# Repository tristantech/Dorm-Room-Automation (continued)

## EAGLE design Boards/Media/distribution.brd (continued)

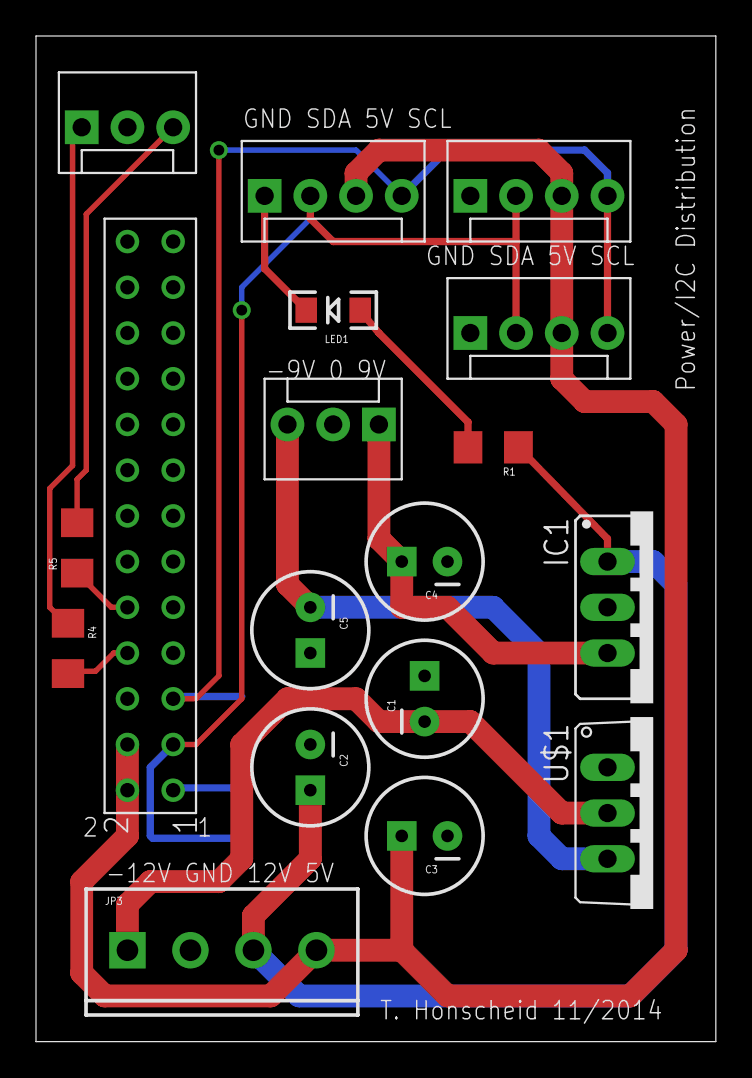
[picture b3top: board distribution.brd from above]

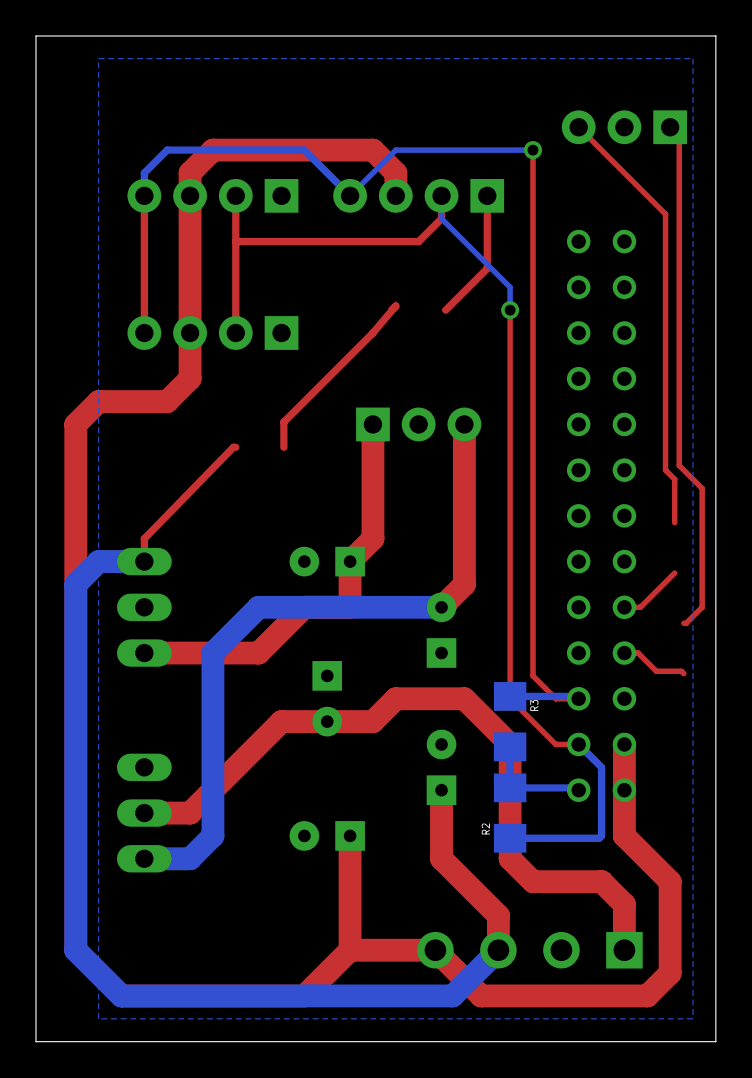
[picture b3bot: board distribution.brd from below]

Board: 2 copper layers, 37.8 x 55.9 mm, 20 parts (2 on the bottom side), 14 nets.

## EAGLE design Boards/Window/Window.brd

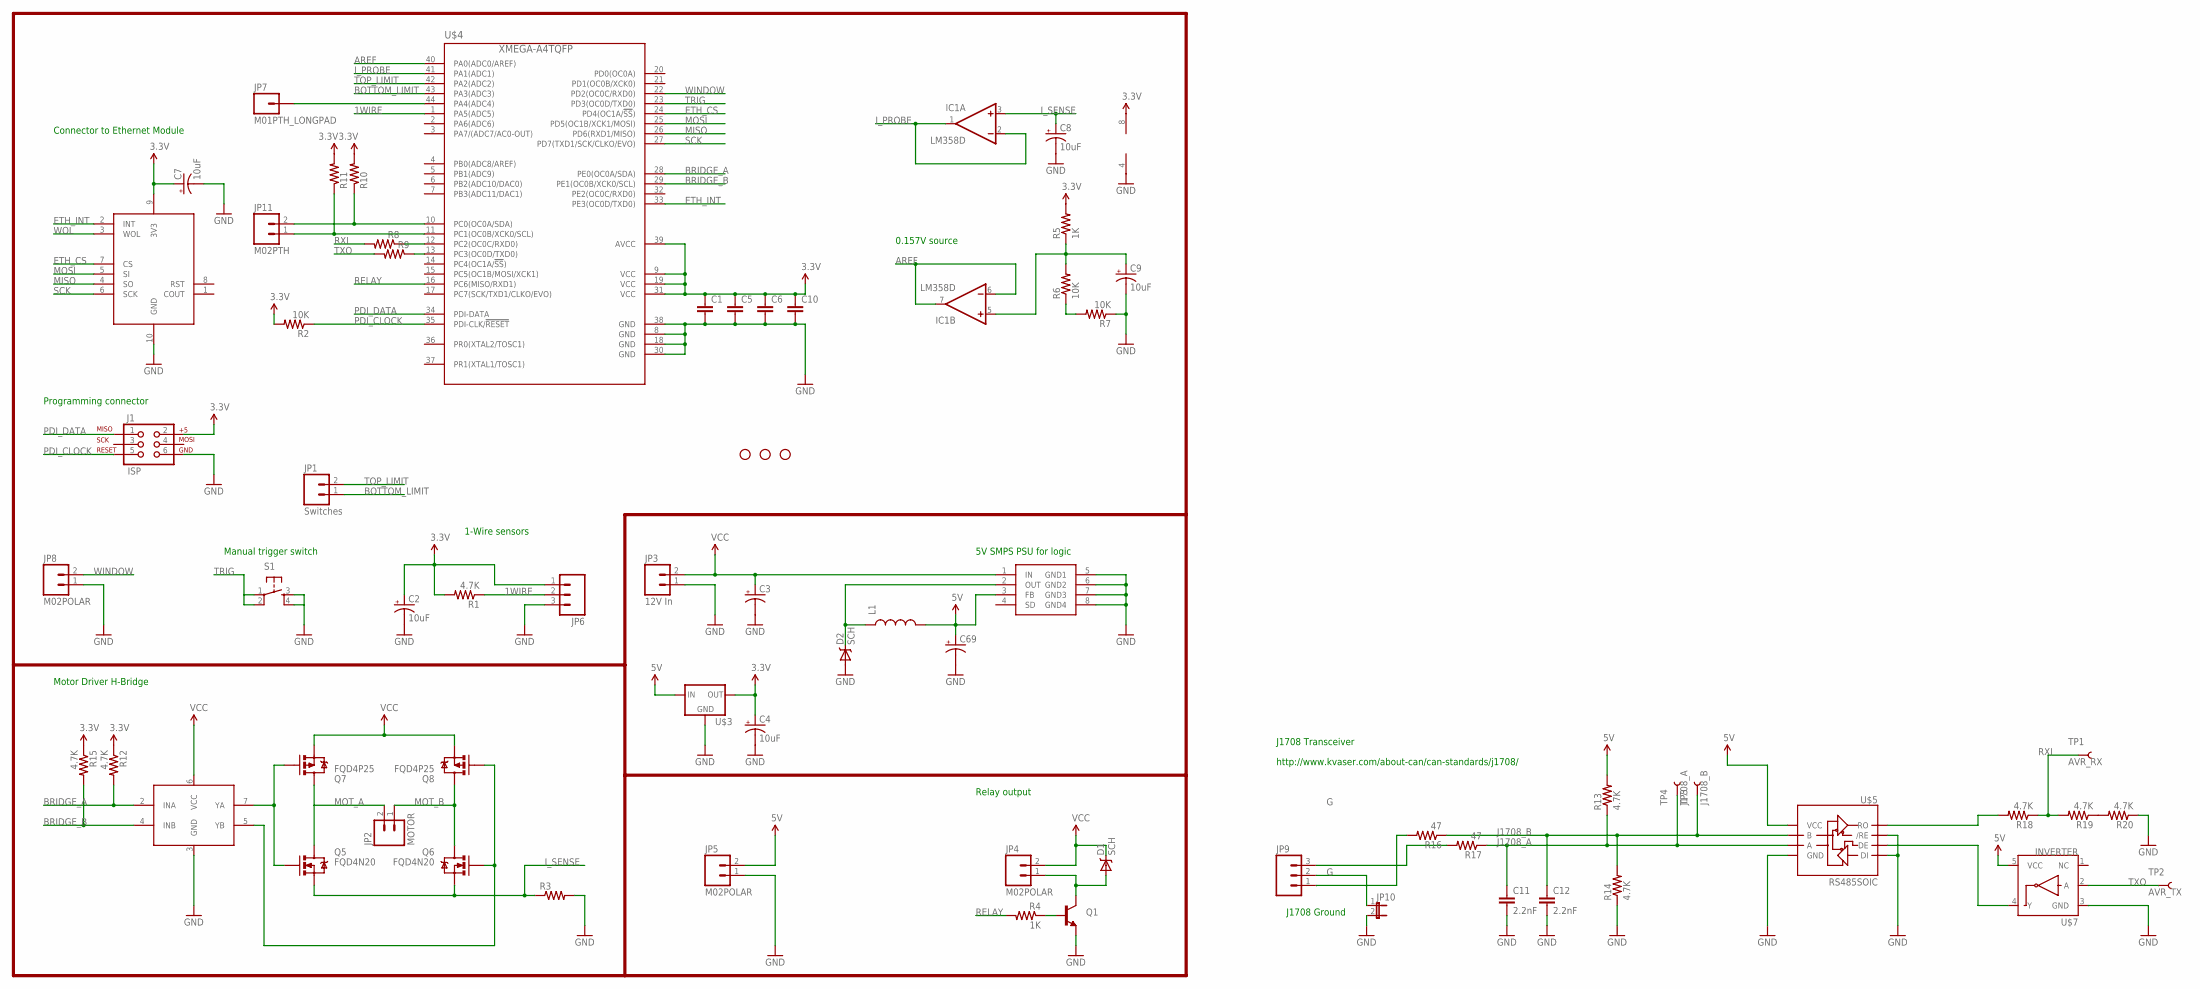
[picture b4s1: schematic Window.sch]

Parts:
C1, C5, C6, C10: CAP0603-CAP; 0603-CAP
C2, C4, C7, C8, C9: 10uF; EIA3216
C3, C69: CAP_POLPTH1; CPOL-RADIAL-100UF-25V
C11, C12: 2.2nF; 0603-CAP
D1, D2: SCH; SMA-DIODE
IC1: LM358D; SO08
J1: ISP; 2X3
JP1: Switches; SCREWTERMINAL-3.5MM-2
JP2: MOTOR; SCREWTERMINAL-3.5MM-2
JP3: 12V In; SCREWTERMINAL-3.5MM-2
JP4, JP5, JP8: M02POLAR; MOLEX-1X2
JP6, JP9: M03POLAR; MOLEX-1X3
JP7: M01PTH_LONGPAD; 1X01_LONGPAD
JP10: JUMPER-2PTH; 1X02
JP11: M02PTH; 1X02
L1: INDUCTOR1206H*; INDUCTOR-1206
Q1: TRANSISTOR_NPNSOT23; SOT23
Q5, Q6: FQD4N20; DPAK
Q7, Q8: FQD4P25; DPAK
R1, R12, R13, R14, R15, R18, R19, R20: 4.7K; 1206
R2, R6, R7: 10K; 1206
R3: RESISTORPTH-1W; AXIAL-0.6
R4, R5: 1K; 1206
R8, R9, R10, R11: RESISTOR0603-RES; 0603-RES
R16, R17: 47; 1206
S1: TAC_SWITCHPTH; TACTILE-PTH
STANDOFF2, STANDOFF3, STANDOFF4: STAND-OFF
TP1: AVR_RX; PAD.03X.05
TP2: AVR_TX; PAD.03X.05
TP3: J1708_B; PAD.03X.05
TP4: J1708_A; PAD.03X.05
U$1: ETHMODULE; 2X5
U$2: AP1509-33; SOIC-8
U$3: V_REG_MIC2920; SOT223
U$4: XMEGA-A4TQFP; TQFP44
U$5: RS485SOIC; SO08
U$6: 4427; SOIC-8
U$7: INVERTER; SOT23-5

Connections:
1WIRE: JP6.2, R1.1, U$4.1 (PA5(ADC5))
3.3V: C1.1, C2.A (+), C4.A (+), C5.1, C6.1, C7.A (+), C10.1, IC1.8 (V+), J1.2, JP6.1, R1.2, R2.2, R5.2, R10.2, R11.2, R12.1, R15.1, U$1.9 (3V3), U$3.3 (OUT), U$4.9 (VCC), U$4.19 (VCC), U$4.31 (VCC), U$4.39 (AVCC)
5V: C69.1 (+), JP5.2, L1.P$2 (2), R13.2, U$2.3 (FB), U$3.1 (IN), U$5.8 (VCC), U$7.5 (VCC)
AREF: IC1.6 (-IN), IC1.7 (OUT), U$4.40 (PA0(ADC0/AREF))
BOTTOM_LIMIT: JP1.1, U$4.43 (PA3(ADC3))
BRIDGE_A: R12.2, U$4.28 (PE0(OC0A/SDA)), U$6.2 (INA)
BRIDGE_B: R15.2, U$4.29 (PE1(OC0B/XCK0/SCL)), U$6.4 (INB)
COUT: U$1.1 (COUT)
ETH_CS: U$1.7 (CS), U$4.24 (PD4(OC1A/!SS!))
ETH_INT: U$1.2 (INT), U$4.33 (PE3(OC0D/TXD0))
G: JP9.2, JP10.1
GND: C1.2, C2.C (-), C3.2 (-), C4.C (-), C5.2, C6.2, C7.C (-), C8.C (-), C9.C (-), C10.2, C11.2, C12.2, C69.2 (-), D2.A, IC1.4 (V-), J1.6, JP3.1, JP5.1, JP6.3, JP8.1, JP10.2, Q1.2 (E), R3.P$2 (2), R7.1, R14.1, R20.1, S1.3, S1.4, U$1.10 (GND), U$2.5 (GND1), U$2.6 (GND2), U$2.7 (GND3), U$2.8 (GND4), U$3.2 (GND), U$4.8 (GND), U$4.18 (GND), U$4.30 (GND), U$4.38 (GND), U$5.2 (/RE), U$5.4 (DI), U$5.5 (GND), U$6.3 (GND), U$7.3 (GND)
I_PROBE: IC1.1 (OUT), IC1.2 (-IN), U$4.41 (PA1(ADC1))
I_SENSE: C8.A (+), IC1.3 (+IN), Q5.3 (S), Q6.3 (S), R3.P$1 (1)
J1708_A: C11.1, R13.1, R17.1, TP4.P$1, U$5.6 (A)
J1708_B: C12.1, R14.2, R16.1, TP3.P$1, U$5.7 (B)
MISO: U$1.4 (SO), U$4.26 (PD6(RXD1/MISO))
MOSI: U$1.5 (SI), U$4.25 (PD5(OC1B/XCK1/MOSI))
MOT_A: JP2.2, Q5.4 (D), Q7.4 (D)
MOT_B: JP2.1, Q6.4 (D), Q8.4 (D)
unnamed: JP11.2, R10.1, U$4.10 (PC0(OC0A/SDA))
unnamed: JP11.1, R11.1, U$4.11 (PC1(OC0B/XCK0/SCL))
unnamed: D2.C, L1.P$1 (1), U$2.2 (OUT)
unnamed: R8.1, U$4.12 (PC2(OC0C/RXD0))
unnamed: D1.A, JP4.1, Q1.3 (C)
unnamed: JP9.1, R16.2
unnamed: R6.1, R7.2
unnamed: Q5.1 (G), Q7.1 (G), U$6.7 (YA)
unnamed: Q1.1 (B), R4.1
unnamed: C9.A (+), IC1.5 (+IN), R5.1, R6.2
unnamed: R9.1, U$4.13 (PC3(OC0D/TXD0))
unnamed: JP9.3, R17.2
unnamed: R18.2, U$5.1 (RO)
unnamed: R19.1, R20.2
unnamed: Q6.1 (G), Q8.1 (G), U$6.5 (YB)
unnamed: U$5.3 (DE), U$7.4 (Y)
unnamed: JP7.1, U$4.44 (PA4(ADC4))
PDI_CLOCK: J1.5, R2.1, U$4.35 (PDI-CLK/!RESET)
PDI_DATA: J1.1, U$4.34 (PDI-DATA)
RELAY: R4.2, U$4.16 (PC6(MISO/RXD1))
RST: U$1.8 (RST)
RXI: R8.2, R18.1, R19.2, TP1.P$1
SCK: U$1.6 (SCK), U$4.27 (PD7(TXD1/SCK/CLKO/EVO))
TOP_LIMIT: JP1.2, U$4.42 (PA2(ADC2))
TRIG: S1.1, S1.2, U$4.23 (PD3(OC0D/TXD0))
TXO: R9.2, TP2.P$1, U$7.2 (A)
VCC: C3.1 (+), D1.C, JP3.2, JP4.2, Q7.3 (S), Q8.3 (S), U$2.1 (IN), U$6.6 (VCC)
WINDOW: JP8.2, U$4.22 (PD2(OC0C/RXD0))
WOL: U$1.3 (WOL)

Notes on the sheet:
Connector to Ethernet Module
Programming connector
1-Wire sensors
Motor Driver H-Bridge
Manual trigger switch
Relay output
0.157V source
5V SMPS PSU for logic
J1708 Ground
J1708 Transceiver
http://www.kvaser.com/about-can/can-standards/j1708/

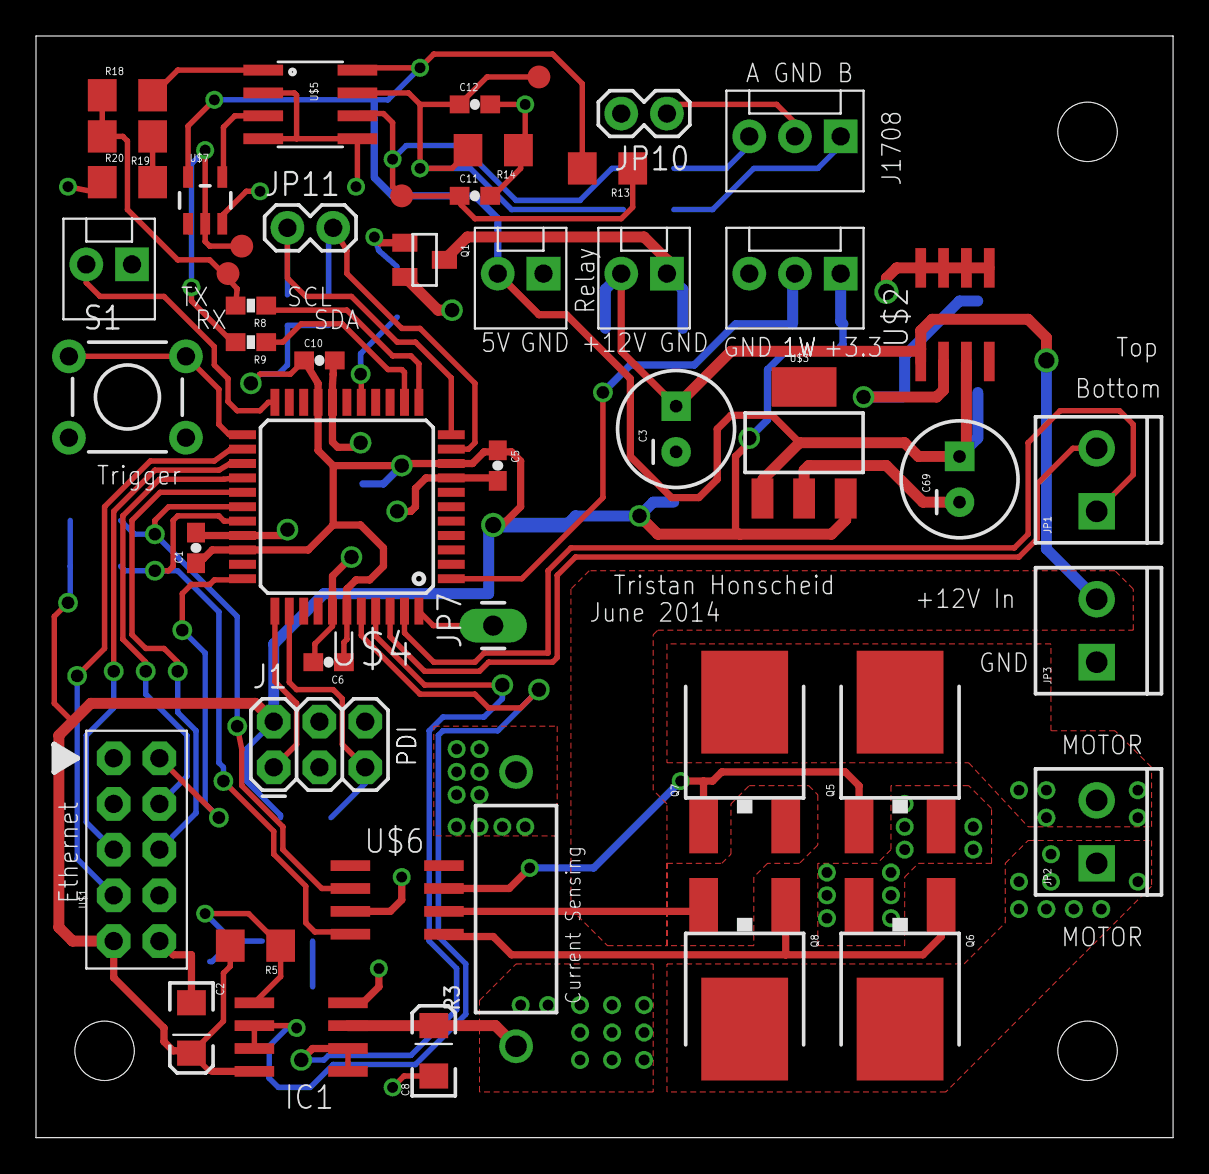
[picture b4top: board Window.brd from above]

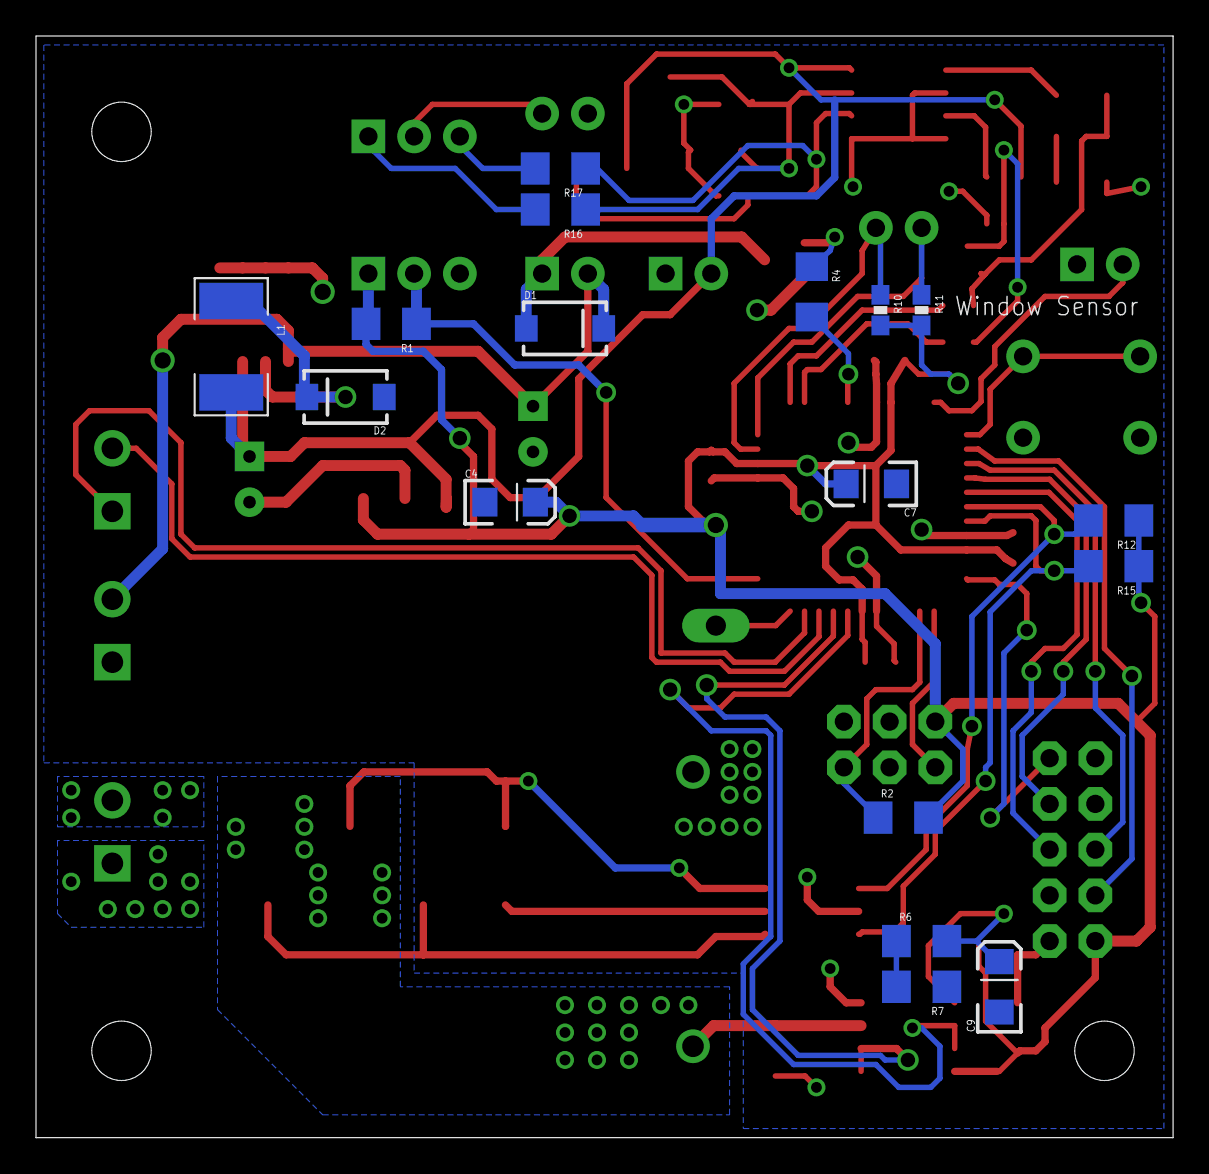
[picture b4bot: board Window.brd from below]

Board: 2 copper layers, 63.2 x 61.2 mm, 69 parts (17 on the bottom side), 46 nets.

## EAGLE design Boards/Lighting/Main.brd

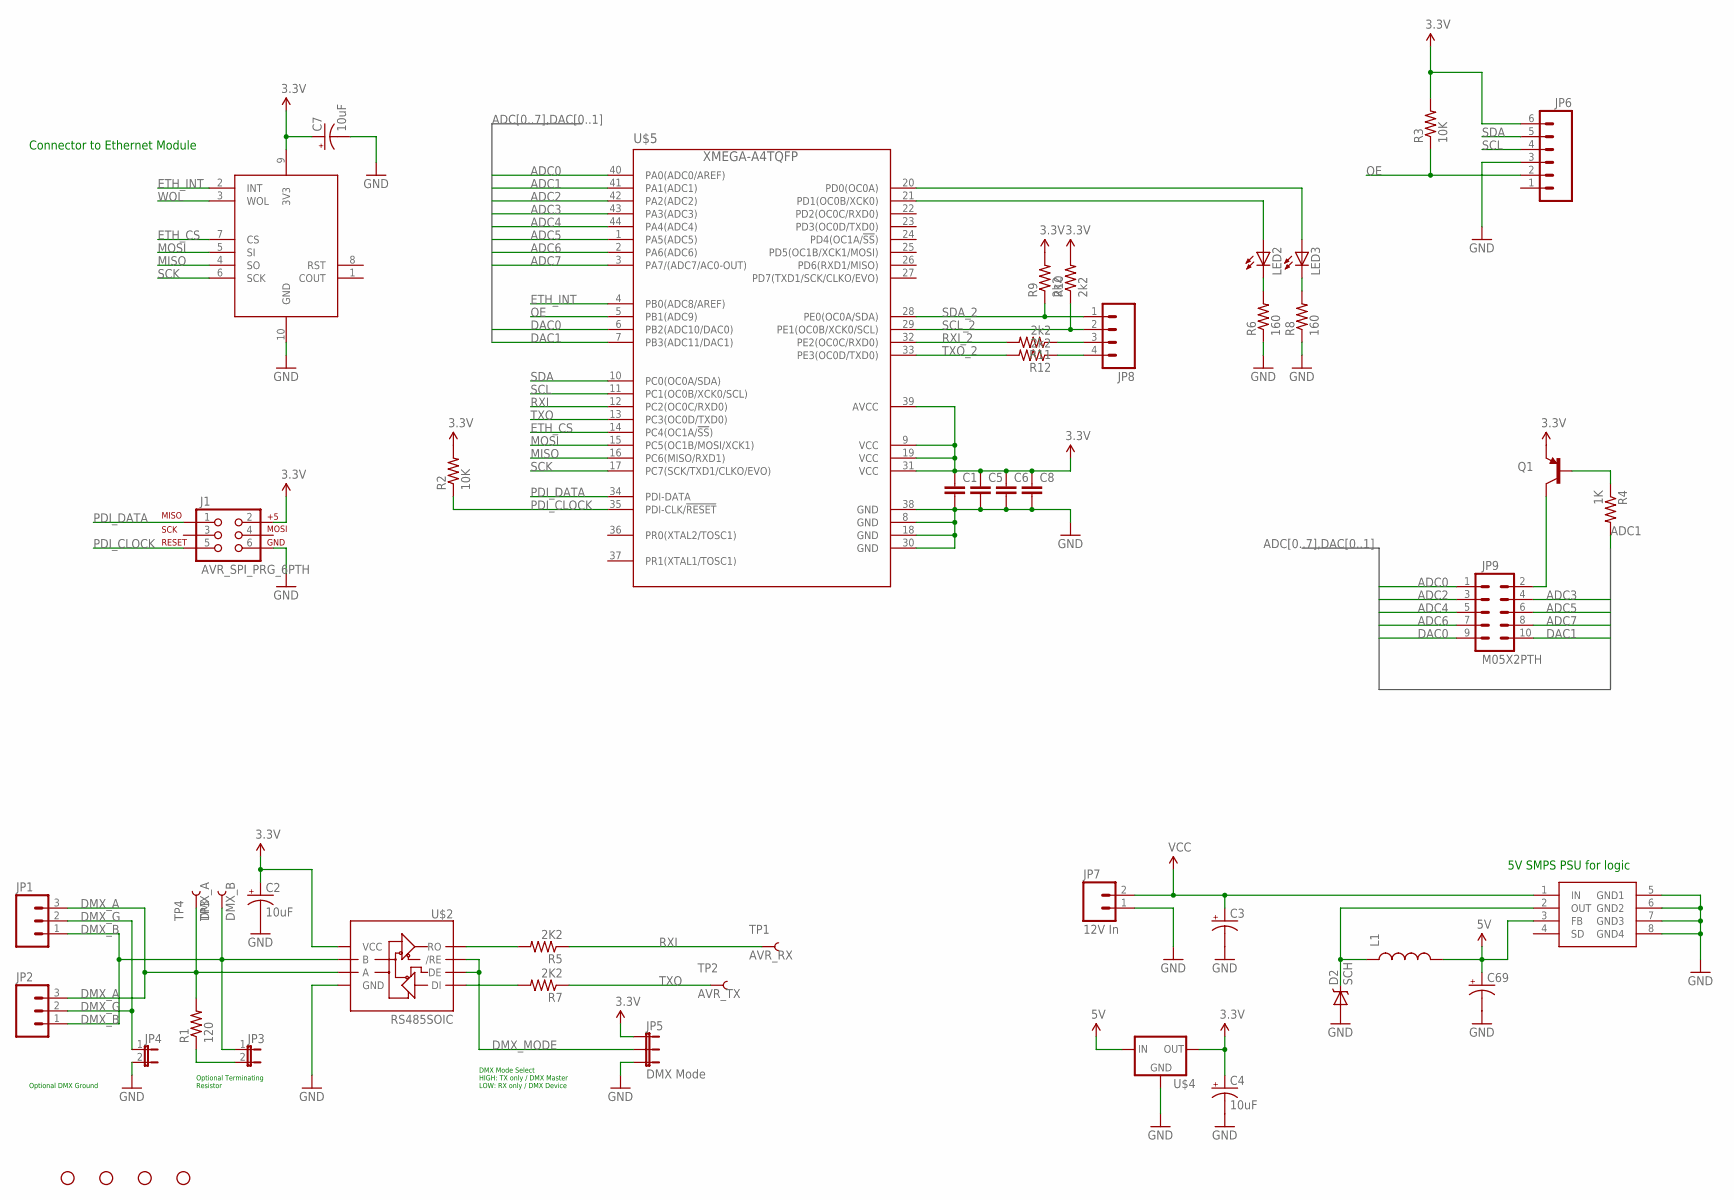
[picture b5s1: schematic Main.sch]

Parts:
C1, C5, C6, C8: CAP0603-CAP; 0603-CAP
C2, C4, C7: 10uF; EIA3216
C3, C69: CAP_POLPTH1; CPOL-RADIAL-100UF-25V
D2: SCH; SMA-DIODE
J1: AVR_SPI_PRG_6PTH; 2X3
JP1, JP2: M03POLAR; MOLEX-1X3
JP3, JP4: JUMPER-2PTH; 1X02
JP5: DMX Mode; 1X03
JP6: M06POLAR; MOLEX-1X6
JP7: 12V In; SCREWTERMINAL-3.5MM-2
JP8: M04PTH; 1X04
JP9: M05X2PTH; AVR_ICSP
L1: INDUCTOR1206H*; INDUCTOR-1206
LED2, LED3: LED5MM
Q1: TRANSISTOR_PNPSMD; SOT23-3
R1: 120; 1206
R2, R3: 10K; 1206
R4: 1K; 1206
R5, R7: 2K2; 1206
R6, R8: 160; 1206
R9, R10, R11, R12: 2k2; 1206
STANDOFF1, STANDOFF2, STANDOFF3, STANDOFF4: STAND-OFF
TP1: AVR_RX; PAD.03X.05
TP2: AVR_TX; PAD.03X.05
TP3: DMX_B; PAD.03X.05
TP4: DMX_A; PAD.03X.05
U$1: ETHMODULE; 2X5
U$2: RS485SOIC; SO08
U$3: AP1509-33; SOIC-8
U$4: V_REG_MIC2920; SOT223
U$5: XMEGA-A4TQFP; TQFP44

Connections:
3.3V: C1.1, C2.A (+), C4.A (+), C5.1, C6.1, C7.A (+), C8.1, J1.2, JP5.1, JP6.6, Q1.2 (E), R2.2, R3.2, R9.2, R10.2, U$1.9 (3V3), U$2.8 (VCC), U$4.3 (OUT), U$5.9 (VCC), U$5.19 (VCC), U$5.31 (VCC), U$5.39 (AVCC)
5V: C69.1 (+), L1.P$2 (2), U$3.3 (FB), U$4.1 (IN)
ADC0: JP9.1, U$5.40 (PA0(ADC0/AREF))
ADC1: R4.2, U$5.41 (PA1(ADC1))
ADC2: JP9.3, U$5.42 (PA2(ADC2))
ADC3: JP9.4, U$5.43 (PA3(ADC3))
ADC4: JP9.5, U$5.44 (PA4(ADC4))
ADC5: JP9.6, U$5.1 (PA5(ADC5))
ADC6: JP9.7, U$5.2 (PA6(ADC6))
ADC7: JP9.8, U$5.3 (PA7/(ADC7/AC0-OUT))
COUT: U$1.1 (COUT)
DAC0: JP9.9, U$5.6 (PB2(ADC10/DAC0))
DAC1: JP9.10, U$5.7 (PB3(ADC11/DAC1))
DMX_A: JP1.3, JP2.3, R1.2, TP4.P$1, U$2.6 (A)
DMX_B: JP1.1, JP2.1, JP3.1, TP3.P$1, U$2.7 (B)
DMX_G: JP1.2, JP2.2, JP4.1
DMX_MODE: JP5.2, U$2.2 (/RE), U$2.3 (DE)
ETH_CS: U$1.7 (CS), U$5.14 (PC4(OC1A/!SS!))
ETH_INT: U$1.2 (INT), U$5.4 (PB0(ADC8/AREF))
GND: C1.2, C2.C (-), C3.2 (-), C4.C (-), C5.2, C6.2, C7.C (-), C8.2, C69.2 (-), D2.A, J1.6, JP4.2, JP5.3, JP6.3, JP7.1, R6.1, R8.1, U$1.10 (GND), U$2.5 (GND), U$3.5 (GND1), U$3.6 (GND2), U$3.7 (GND3), U$3.8 (GND4), U$4.2 (GND), U$5.8 (GND), U$5.18 (GND), U$5.30 (GND), U$5.38 (GND)
MISO: U$1.4 (SO), U$5.16 (PC6(MISO/RXD1))
MOSI: U$1.5 (SI), U$5.15 (PC5(OC1B/MOSI/XCK1))
unnamed: D2.C, L1.P$1 (1), U$3.2 (OUT)
unnamed: JP8.3, R11.1
unnamed: R7.2, U$2.4 (DI)
unnamed: R5.2, U$2.1 (RO)
unnamed: LED3.A, U$5.20 (PD0(OC0A))
unnamed: LED2.A, U$5.21 (PD1(OC0B/XCK0))
unnamed: JP9.2, Q1.3 (C)
unnamed: JP3.2, R1.1
unnamed: Q1.1 (B), R4.1
unnamed: LED2.K (C), R6.2
unnamed: LED3.K (C), R8.2
unnamed: JP8.4, R12.1
OE: JP6.2, R3.1, U$5.5 (PB1(ADC9))
PDI_CLOCK: J1.5, R2.1, U$5.35 (PDI-CLK/!RESET)
PDI_DATA: J1.1, U$5.34 (PDI-DATA)
RST: U$1.8 (RST)
RXI: R5.1, TP1.P$1, U$5.12 (PC2(OC0C/RXD0))
RXI_2: R11.2, U$5.32 (PE2(OC0C/RXD0))
SCK: U$1.6 (SCK), U$5.17 (PC7(SCK/TXD1/CLKO/EVO))
SCL: JP6.4, U$5.11 (PC1(OC0B/XCK0/SCL))
SCL_2: JP8.2, R10.1, U$5.29 (PE1(OC0B/XCK0/SCL))
SDA: JP6.5, U$5.10 (PC0(OC0A/SDA))
SDA_2: JP8.1, R9.1, U$5.28 (PE0(OC0A/SDA))
TXO: R7.1, TP2.P$1, U$5.13 (PC3(OC0D/TXD0))
TXO_2: R12.2, U$5.33 (PE3(OC0D/TXD0))
VCC: C3.1 (+), JP7.2, U$3.1 (IN)
WOL: U$1.3 (WOL)

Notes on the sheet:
Optional Terminating Resistor
Optional DMX Ground
DMX Mode Select HIGH: TX only / DMX Master LOW: RX only / DMX Device
Connector to Ethernet Module
5V SMPS PSU for logic

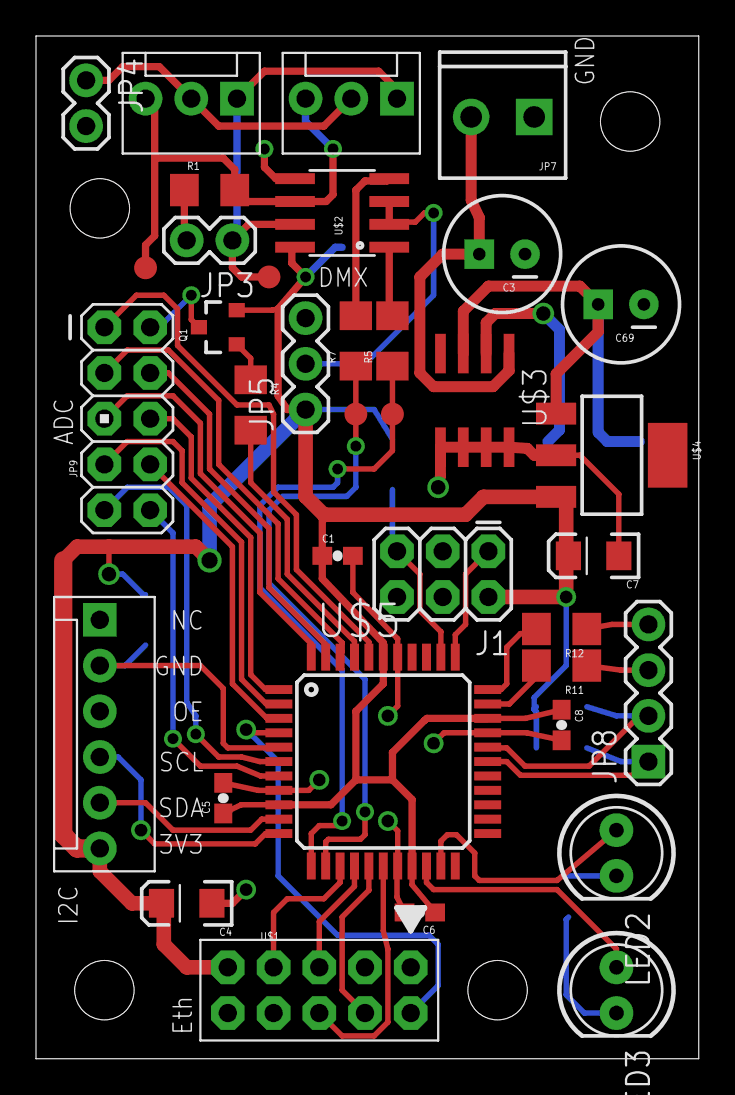
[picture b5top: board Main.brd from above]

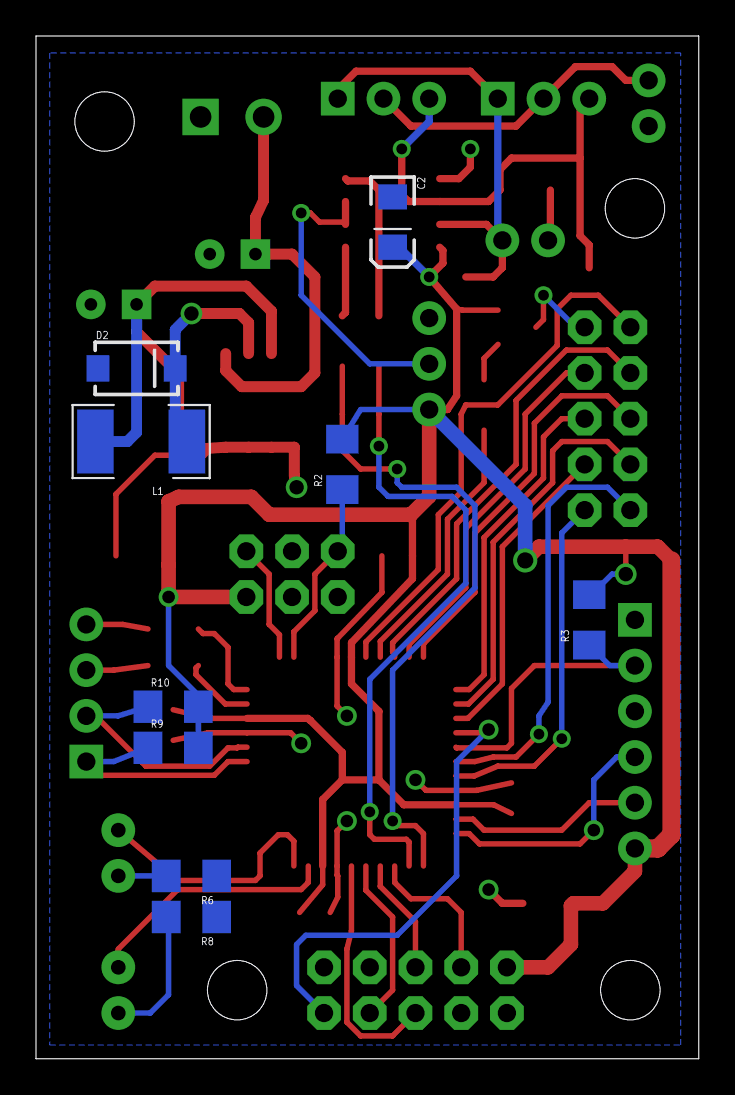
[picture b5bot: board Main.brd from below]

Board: 2 copper layers, 36.8 x 56.8 mm, 49 parts (9 on the bottom side), 46 nets.

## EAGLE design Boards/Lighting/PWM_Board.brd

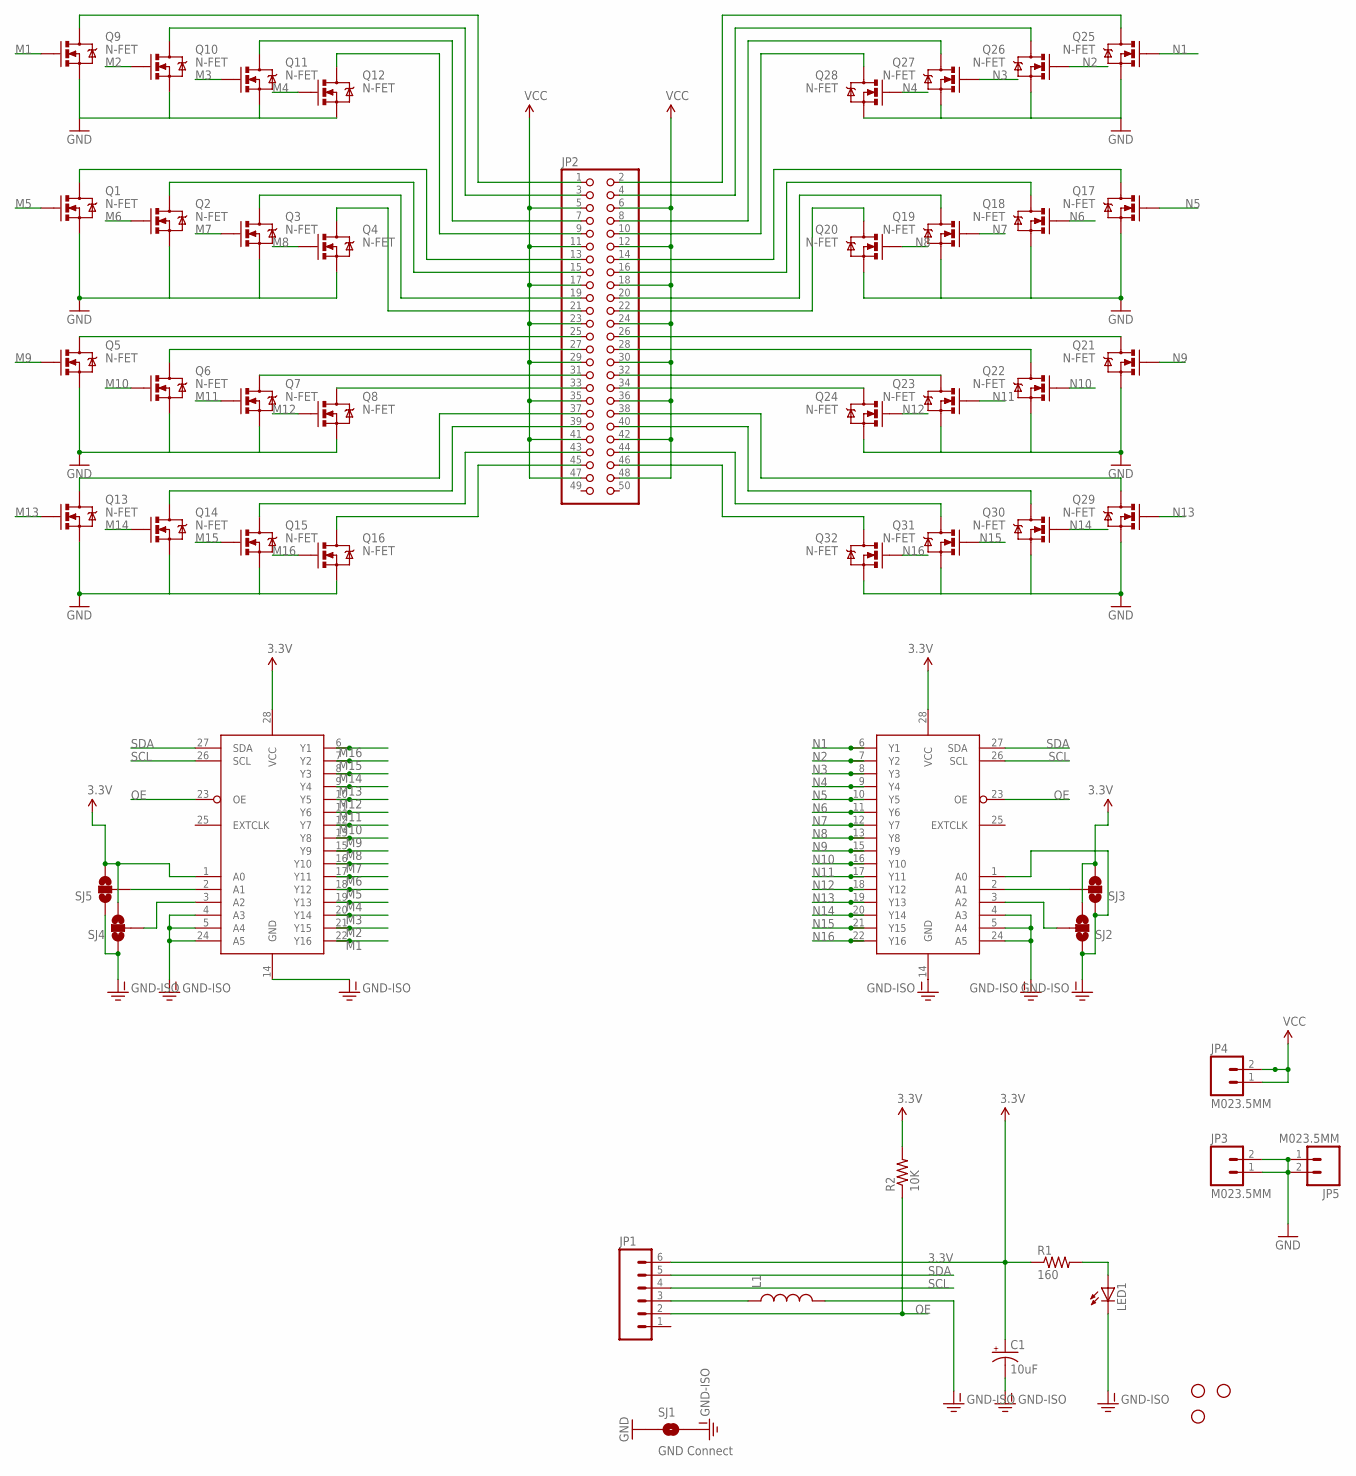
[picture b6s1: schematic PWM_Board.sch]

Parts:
C1: 10uF; EIA3216
JP1: M06POLAR; MOLEX-1X6
JP2: PINHD-2X25; 2X25
JP3, JP4, JP5: M023.5MM; SCREWTERMINAL-3.5MM-2
L1: INDUCTOR1206H*; INDUCTOR-1206
LED1: LED-FKIT-1206; FKIT-LED-1206
Q1, Q2, Q3, Q4, Q5, Q6, Q7, Q8, Q9, Q10, Q11, Q12, Q13, Q14, Q15, Q16, Q17, Q18, Q19, Q20, Q21, Q22, Q23, Q24, Q25, Q26, Q27, Q28, Q29, Q30, Q31, Q32: N-FET; SOT23
R1: 160; 1206
R2: 10K; 1206
SJ1: GND Connect; SJ_2S
SJ2, SJ3, SJ4, SJ5: SOLDERJUMPER_2WAYS; SJ_3
STANDOFF1, STANDOFF3, STANDOFF4: STAND-OFF
U$2, U$3: PCA9685; TSSOP28

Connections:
3.3V: C1.A (+), JP1.6, R1.1, R2.2, SJ2.3, SJ3.3, SJ4.3, SJ5.3, U$2.28 (VCC), U$3.1 (A0), U$3.28 (VCC)
GND: JP3.1, JP3.2, JP5.1, JP5.2, Q1.2 (S), Q2.2 (S), Q3.2 (S), Q4.2 (S), Q5.2 (S), Q6.2 (S), Q7.2 (S), Q8.2 (S), Q9.2 (S), Q10.2 (S), Q11.2 (S), Q12.2 (S), Q13.2 (S), Q14.2 (S), Q15.2 (S), Q16.2 (S), Q17.2 (S), Q18.2 (S), Q19.2 (S), Q20.2 (S), Q21.2 (S), Q22.2 (S), Q23.2 (S), Q24.2 (S), Q25.2 (S), Q26.2 (S), Q27.2 (S), Q28.2 (S), Q29.2 (S), Q30.2 (S), Q31.2 (S), Q32.2 (S), SJ1.1
GND-ISO: C1.C (-), L1.P$2 (2), LED1.C, SJ1.2, SJ2.1, SJ3.1, SJ4.1, SJ5.1, U$2.1 (A0), U$2.4 (A3), U$2.5 (A4), U$2.14 (GND), U$2.24 (A5), U$3.4 (A3), U$3.5 (A4), U$3.14 (GND), U$3.24 (A5)
M1: Q9.1 (G), U$3.22 (Y16)
M2: Q10.1 (G), U$3.21 (Y15)
M3: Q11.1 (G), U$3.20 (Y14)
M4: Q12.1 (G), U$3.19 (Y13)
M5: Q1.1 (G), U$3.18 (Y12)
M6: Q2.1 (G), U$3.17 (Y11)
M7: Q3.1 (G), U$3.16 (Y10)
M8: Q4.1 (G), U$3.15 (Y9)
M9: Q5.1 (G), U$3.13 (Y8)
M10: Q6.1 (G), U$3.12 (Y7)
M11: Q7.1 (G), U$3.11 (Y6)
M12: Q8.1 (G), U$3.10 (Y5)
M13: Q13.1 (G), U$3.9 (Y4)
M14: Q14.1 (G), U$3.8 (Y3)
M15: Q15.1 (G), U$3.7 (Y2)
M16: Q16.1 (G), U$3.6 (Y1)
N1: Q25.1 (G), U$2.6 (Y1)
N2: Q26.1 (G), U$2.7 (Y2)
N3: Q27.1 (G), U$2.8 (Y3)
N4: Q28.1 (G), U$2.9 (Y4)
N5: Q17.1 (G), U$2.10 (Y5)
N6: Q18.1 (G), U$2.11 (Y6)
N7: Q19.1 (G), U$2.12 (Y7)
N8: Q20.1 (G), U$2.13 (Y8)
N9: Q21.1 (G), U$2.15 (Y9)
N10: Q22.1 (G), U$2.16 (Y10)
N11: Q23.1 (G), U$2.17 (Y11)
N12: Q24.1 (G), U$2.18 (Y12)
N13: Q29.1 (G), U$2.19 (Y13)
N14: Q30.1 (G), U$2.20 (Y14)
N15: Q31.1 (G), U$2.21 (Y15)
N16: Q32.1 (G), U$2.22 (Y16)
unnamed: JP1.3, L1.P$1 (1)
unnamed: JP2.1, Q9.3 (D)
unnamed: JP2.3, Q10.3 (D)
unnamed: JP2.7, Q11.3 (D)
unnamed: JP2.9, Q12.3 (D)
unnamed: JP2.13, Q1.3 (D)
unnamed: JP2.15, Q2.3 (D)
unnamed: JP2.19, Q3.3 (D)
unnamed: JP2.21, Q4.3 (D)
unnamed: JP2.25, Q5.3 (D)
unnamed: LED1.A, R1.2
unnamed: JP2.27, Q6.3 (D)
unnamed: JP2.31, Q7.3 (D)
unnamed: JP2.33, Q8.3 (D)
unnamed: JP2.37, Q13.3 (D)
unnamed: JP2.39, Q14.3 (D)
unnamed: JP2.43, Q15.3 (D)
unnamed: JP2.45, Q16.3 (D)
unnamed: JP2.2, Q25.3 (D)
unnamed: JP2.4, Q26.3 (D)
unnamed: JP2.8, Q27.3 (D)
unnamed: JP2.10, Q28.3 (D)
unnamed: JP2.14, Q17.3 (D)
unnamed: JP2.16, Q18.3 (D)
unnamed: JP2.20, Q19.3 (D)
unnamed: JP2.22, Q20.3 (D)
unnamed: JP2.26, Q21.3 (D)
unnamed: JP2.28, Q22.3 (D)
unnamed: JP2.32, Q23.3 (D)
unnamed: JP2.34, Q24.3 (D)
unnamed: JP2.38, Q29.3 (D)
unnamed: JP2.40, Q30.3 (D)
unnamed: JP2.44, Q31.3 (D)
unnamed: JP2.46, Q32.3 (D)
unnamed: SJ3.2, U$2.2 (A1)
unnamed: SJ2.2, U$2.3 (A2)
unnamed: SJ5.2, U$3.2 (A1)
unnamed: SJ4.2, U$3.3 (A2)
OE: JP1.2, R2.1, U$2.23 (OE), U$3.23 (OE)
SCL: JP1.4, U$2.26 (SCL), U$3.26 (SCL)
SDA: JP1.5, U$2.27 (SDA), U$3.27 (SDA)
VCC: JP2.5, JP2.6, JP2.11, JP2.12, JP2.17, JP2.18, JP2.23, JP2.24, JP2.29, JP2.30, JP2.35, JP2.36, JP2.41, JP2.42, JP2.47, JP2.48, JP4.1, JP4.2

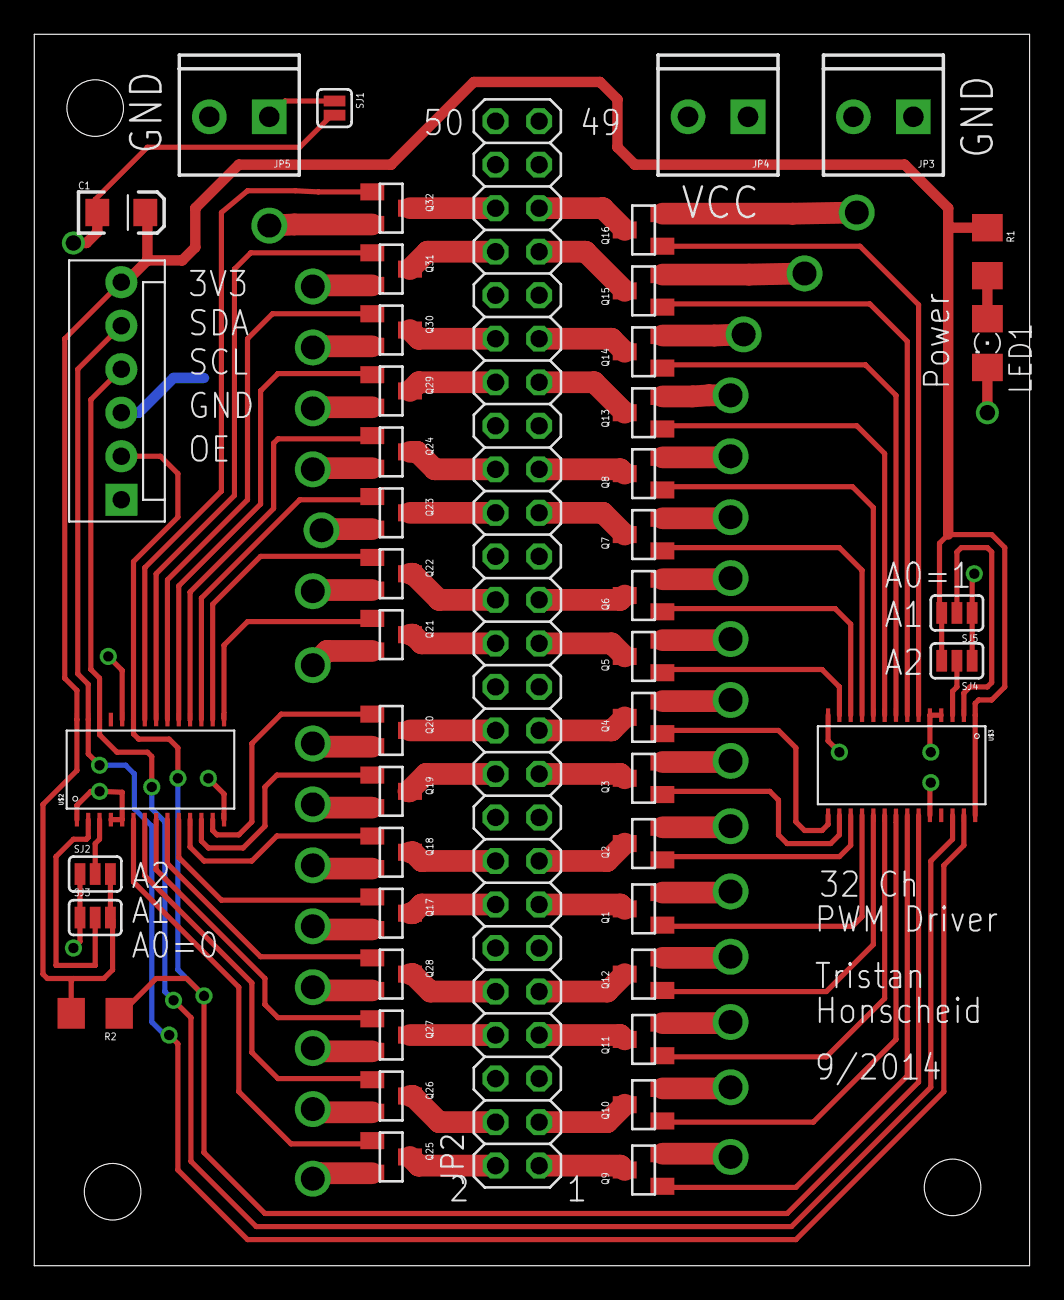
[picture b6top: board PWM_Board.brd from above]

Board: 2 copper layers, 58.1 x 71.9 mm, 52 parts (1 on the bottom side), 77 nets.
